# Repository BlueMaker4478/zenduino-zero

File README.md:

# zenduino-zero
STM32 Based Microcontroller Board

I used STM32F103C8T6 and STM32F030C8T6.
This board designed for F030, but the other one works too.

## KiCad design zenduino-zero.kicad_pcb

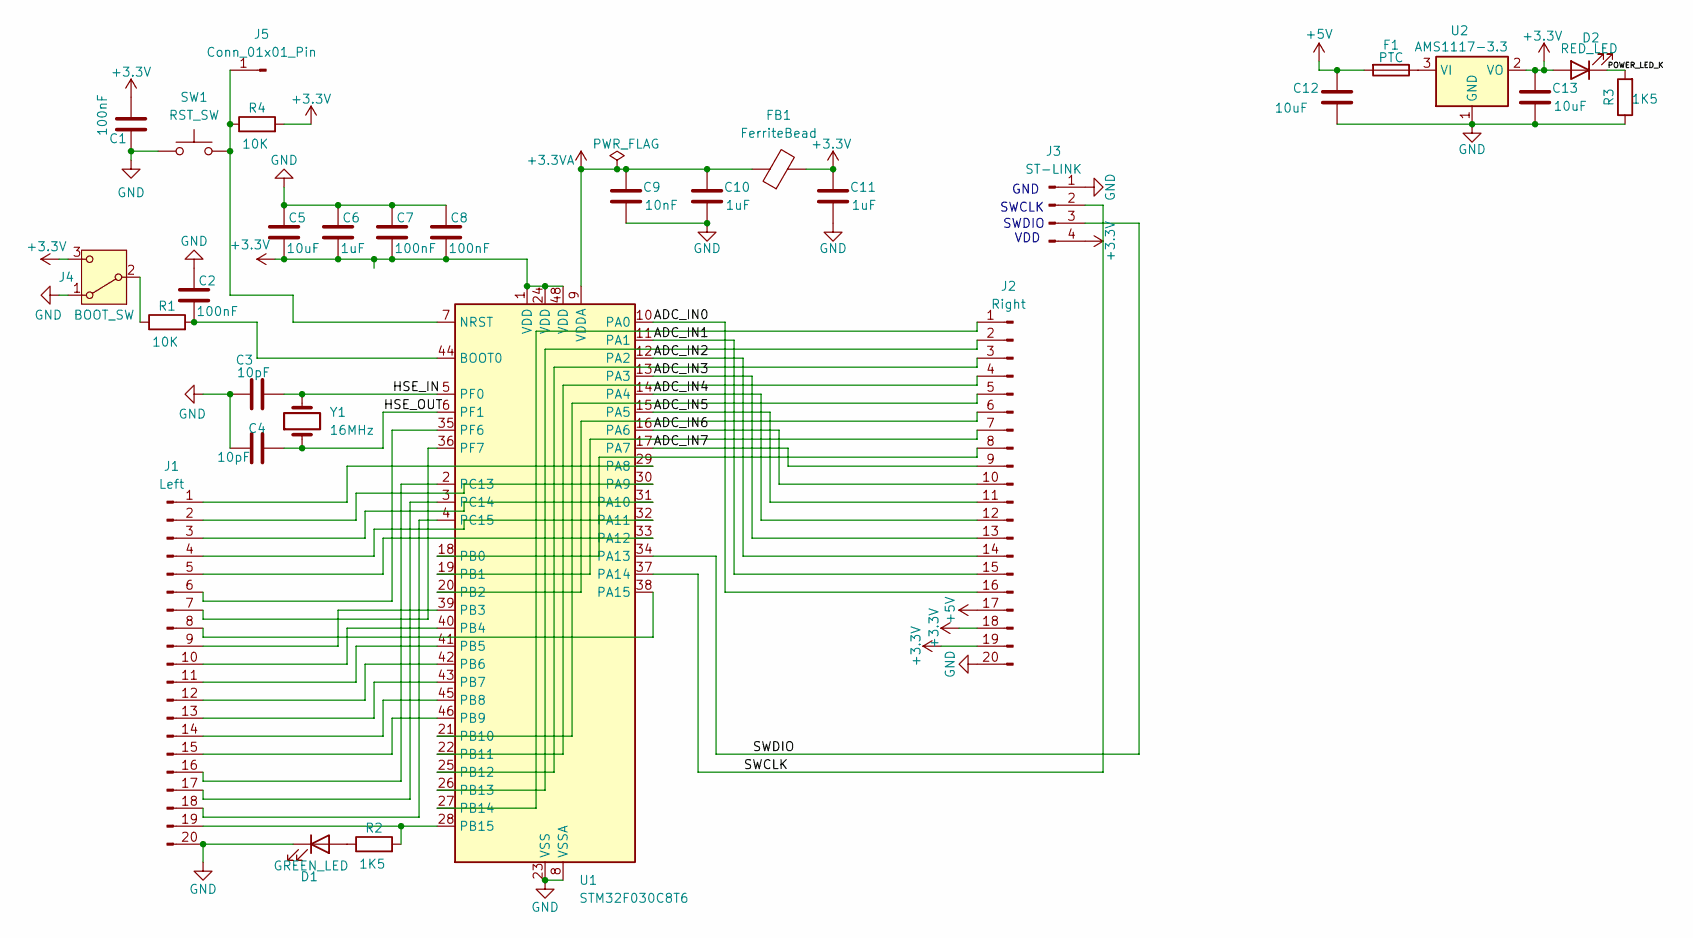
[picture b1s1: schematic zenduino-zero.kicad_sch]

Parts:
C1, C2, C7, C8: 100nF; C_0805_2012Metric_Pad1.18x1.45mm_HandSolder
C3, C4: 10pF; C_0805_2012Metric_Pad1.18x1.45mm_HandSolder
C5, C12, C13: 10uF; C_1206_3216Metric_Pad1.33x1.80mm_HandSolder
C6, C10, C11: 1uF; C_1206_3216Metric_Pad1.33x1.80mm_HandSolder
C9: 10nF; C_0805_2012Metric_Pad1.18x1.45mm_HandSolder
D1: GREEN_LED; LED_1206_3216Metric_Pad1.42x1.75mm_HandSolder
D2: RED_LED; LED_1206_3216Metric_Pad1.42x1.75mm_HandSolder
F1: PTC; Fuse_1206_3216Metric_Pad1.42x1.75mm_HandSolder
FB1: FerriteBead; R_0805_2012Metric_Pad1.20x1.40mm_HandSolder
J1: Left; PinHeader_1x20_P2.54mm_Vertical
J2: Right; PinHeader_1x20_P2.54mm_Vertical
J3: ST-LINK; PinHeader_1x04_P2.54mm_Vertical
J4: BOOT_SW; PinHeader_1x03_P2.54mm_Vertical
J5: Conn_01x01_Pin; PinHeader_1x01_P2.54mm_Vertical
R1, R4: 10K; R_0805_2012Metric_Pad1.20x1.40mm_HandSolder
R2, R3: 1K5; R_0805_2012Metric_Pad1.20x1.40mm_HandSolder
SW1: RST_SW; SW_SPST_B3U-1000P
U1: STM32F030C8T6; LQFP-48_7x7mm_P0.5mm
U2: AMS1117-3.3; SOT-223-3_TabPin2
Y1: 16MHz; Crystal_SMD_TXC_7A-2Pin_5x3.2mm

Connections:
+3.3V: C1.2, C5.2, C6.2, C7.2, C8.2, C11.1, C13.1, D2.2 (A), FB1.2, J2.18, J2.19, J3.4, J4.3 (C), R4.2, U1.1 (VDD), U1.24 (VDD), U1.48 (VDD), U2.2 (VO)
+3.3VA: C9.1, C10.1, FB1.1, U1.9 (VDDA)
+5V: C12.1, F1.2, J2.17
/ADC_IN0: J2.16, U1.10 (PA0)
/ADC_IN1: J2.15, U1.11 (PA1)
/ADC_IN2: J2.14, U1.12 (PA2)
/ADC_IN3: J2.13, U1.13 (PA3)
/ADC_IN4: J2.12, U1.14 (PA4)
/ADC_IN5: J2.11, U1.15 (PA5)
/ADC_IN6: J2.10, U1.16 (PA6)
/ADC_IN7: J2.9, U1.17 (PA7)
/HSE_IN: C3.1, U1.5 (PF0), Y1.2
/HSE_OUT: C4.1, U1.6 (PF1), Y1.1
/POWER_LED_K: D2.1 (K), R3.2
/SWCLK: J3.2, U1.37 (PA14)
/SWDIO: J3.3, U1.34 (PA13)
/USB_N: J1.4, U1.32 (PA11)
/USB_P: J1.5, U1.33 (PA12)
GND: C1.1, C2.1, C3.2, C4.2, C5.1, C6.1, C7.1, C8.1, C9.2, C10.2, C11.2, C12.2, C13.2, D1.1 (K), J1.20, J2.20, J3.1, J4.1 (A), R3.1, SW1.1, U1.8 (VSSA), U1.23 (VSS), U1.47 (VSS), U2.1 (GND)
unnamed: D1.2 (A), R2.1
unnamed: J1.1, U1.29 (PA8)
unnamed: J1.2, U1.30 (PA9)
unnamed: J1.3, U1.31 (PA10)
unnamed: J1.6, U1.35 (PF6)
unnamed: J1.7, U1.36 (PF7)
unnamed: J1.8, U1.38 (PA15)
unnamed: J1.9, U1.39 (PB3)
unnamed: J1.10, U1.40 (PB4)
unnamed: J1.11, U1.41 (PB5)
unnamed: J1.12, U1.42 (PB6)
unnamed: J1.13, U1.43 (PB7)
unnamed: J1.14, U1.45 (PB8)
unnamed: J1.15, U1.46 (PB9)
unnamed: J1.16, U1.2 (PC13)
unnamed: J1.17, U1.3 (PC14)
unnamed: J1.18, U1.4 (PC15)
unnamed: J1.19, R2.2, U1.28 (PB15)
unnamed: J2.1, U1.27 (PB14)
unnamed: J2.2, U1.26 (PB13)
unnamed: J2.3, U1.25 (PB12)
unnamed: J2.4, U1.22 (PB11)
unnamed: J2.5, U1.21 (PB10)
unnamed: J2.6, U1.20 (PB2)
unnamed: J2.7, U1.19 (PB1)
unnamed: J2.8, U1.18 (PB0)
unnamed: J4.2 (B), R1.1
unnamed: J5.1, R4.1, SW1.2, U1.7 (NRST)
unnamed: C2.2, R1.2, U1.44 (BOOT0)
unnamed: F1.1, U2.3 (VI)

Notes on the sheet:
SWCLK
SWDIO
VDD
GND

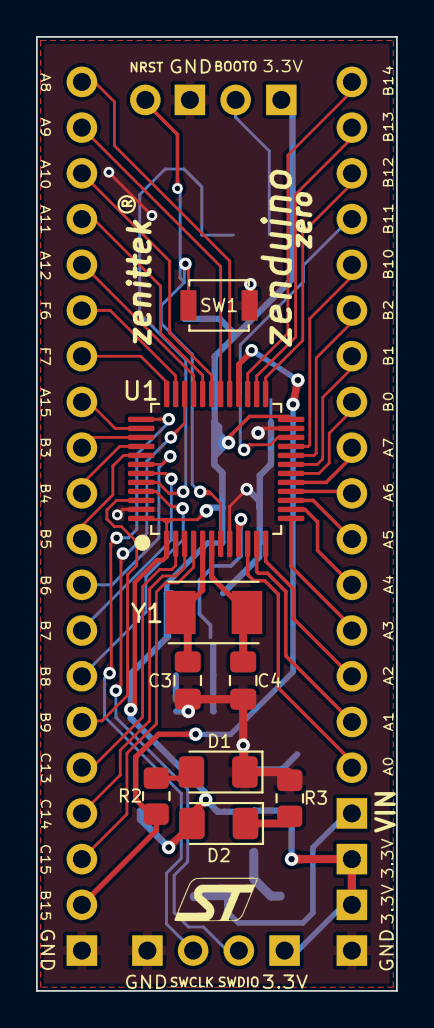
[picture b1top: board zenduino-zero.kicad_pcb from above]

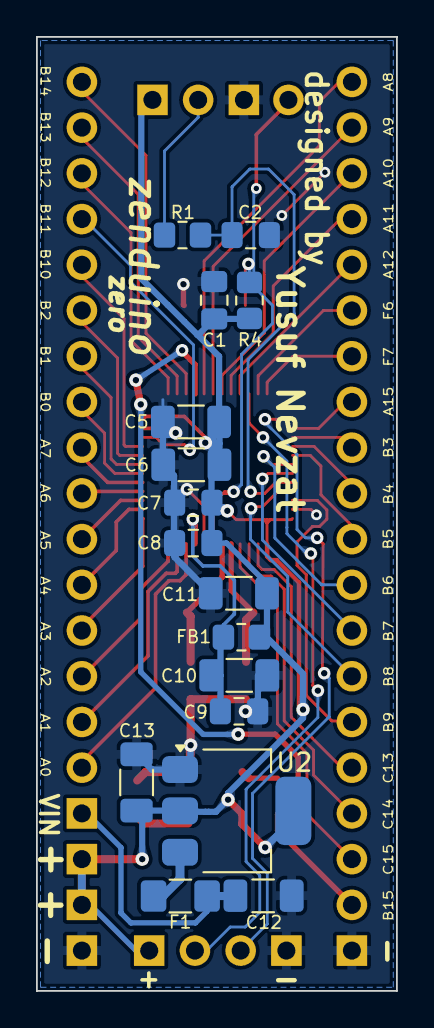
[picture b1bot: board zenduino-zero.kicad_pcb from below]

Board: 2 copper layers, 20.0 x 53.0 mm, 30 parts (18 on the bottom side), 49 nets.

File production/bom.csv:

Designator,Footprint,Quantity,Value,LCSC Part #
"C1, C2, C7, C8",0805,4,100nF,
"C10, C11, C6",1206,3,1uF,
"C12, C13",1206,2,470uF,
"C3, C4",0805,2,10pF,
C5,1206,1,10uF,
C9,0805,1,10nF,
D1,1206,1,GREEN_LED,
D2,1206,1,RED_LED,
F1,1206,1,PTC,
FB1,0805,1,FerriteBead,
J1,PinHeader_1x20_P2.54mm_Vertical,1,Left,
J2,PinHeader_1x20_P2.54mm_Vertical,1,Right,
J3,PinHeader_1x04_P2.54mm_Vertical,1,ST-LINK,
J4,PinHeader_1x03_P2.54mm_Vertical,1,BOOT_SW,
J5,PinHeader_1x01_P2.54mm_Vertical,1,Conn_01x01_Pin,
"R1, R4",0805,2,10K,
"R2, R3",0805,2,1K5,
SW1,SW_SPST_B3U-1000P,1,RST_SW,
U1,LQFP-48_7x7mm_P0.5mm,1,STM32F030C8T6,
U2,SOT-223-3_TabPin2,1,AMS1117-3.3,
Y1,Crystal_SMD_TXC_7A-2Pin_5x3.2mm,1,16MHz,

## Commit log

2025-07-24 README.md
